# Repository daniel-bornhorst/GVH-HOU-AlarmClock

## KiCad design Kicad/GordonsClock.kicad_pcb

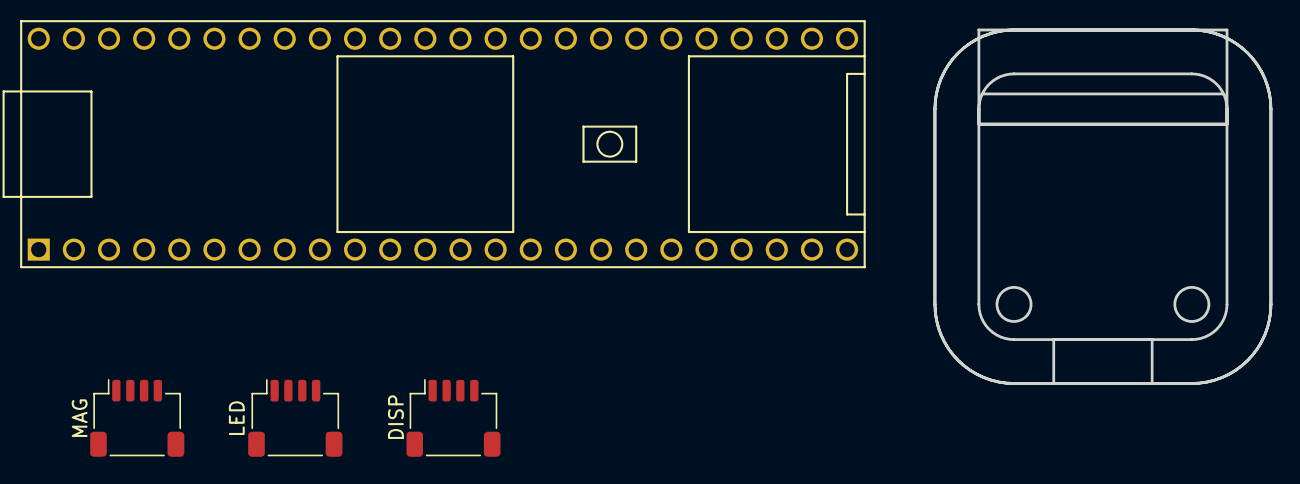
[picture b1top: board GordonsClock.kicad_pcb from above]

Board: 2 copper layers, 24.3 x 25.6 mm, 4 parts (0 on the bottom side), 8 nets, no tracks yet.

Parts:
DISP: JST_SH_SM04B-SRSS-TB_1x04-1MP_P1.00mm_Horizontal
LED: JST_SH_SM04B-SRSS-TB_1x04-1MP_P1.00mm_Horizontal
MAG: JST_SH_SM04B-SRSS-TB_1x04-1MP_P1.00mm_Horizontal
U1: Teensy4.1; Teensy41_minimal

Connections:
+3V3: DISP.2 (3.3VDC), MAG.2 (3.3VDC), U1.46 (3V3)
+5V: LED.2 (5VDC), U1.48 (VIN)
DISP_SCL: DISP.4 (SCL), U1.16 (24_A10_TX6_SCL2)
DISP_SDA: DISP.3 (SDA), U1.17 (25_A11_RX6_SDA2)
GND: DISP.1 (GND), LED.1 (GND), MAG.1 (GND), U1.1 (GND), U1.34 (GND), U1.47 (GND)
MAG_SCL: MAG.4 (SCL), U1.41 (19_A5_SCL)
MAG_SDA: MAG.3 (SDA), U1.40 (18_A4_SDA)
PIXEL_DATA: LED.3 (DATA), U1.8 (6_OUT1D)

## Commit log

2023-10-09 Added return to idle mode timeout
    After a certain amount of time the clock returns to its "Idle" state.
2023-10-09 Start in IDLE mode
2023-10-09 Refactored to use custom HT16k33 and i2c diver
    Using a non blocking i2c driver to hopefully prevent audio playback glitches.
2023-10-09 Added randomization mask and elapsedMillis timer
2023-10-09 Added character lookup and string scrolling
    Still very buggy
2023-10-09 Fixed scrolling txt rest bug
2023-10-10 Disabled Scrolling mode
2023-10-10 Using new i2c driver directy, added audio
    Using i2c driver for teensy directly vs use the Wire library wrapper.
2023-10-11 More file refactoring and organizing. Implemented display class state.
2023-10-14 Added VU meter mode, Updated animation engine, added animation
    Updated animation engine to instantly switch animations and load first frame data properly
2023-10-19 Added proper glitch animation
2023-10-19 VU Meter adjustments
2023-10-21 Added tuning pot routine, display setters
2023-10-25 Changer tuner from pot to quad encoder
2023-10-25 added auto glitch ie attract mode
2023-10-25 Completed text scrolling
2023-10-26 Changed names ie atm->sleep etc..
2023-10-26 Added a bunch of animations and one shot mode
2023-10-27 animation cleanup
2023-10-29 QTPY Branch - experimental
2023-10-29 Got it working on the py and added some animations
2023-10-30 Button and switch integration
2023-11-04 Got network working and added watchdog routine
2023-11-04 Added OSC message receive
2023-11-09 Added simple clock mode
2023-11-11 updated power couple IP
2023-11-22 code tidying
2023-11-25 Manually Merged QTPY & main branches
    NOTE: Modified teensy NativeEthernet library to keep it from hanging when no cable is plugged in.
    At line 293 Replaced:
    while(!link_status){ // original loop
    }
    With:
    uint16_t escape_counter = 0;
2023-11-30 Minute animation changes
2023-11-30 Updated minutes animation...again
2023-12-06 Added USE_NETWORK directive, cleaned up min animation
2023-12-06 Made wake animation more intricate
2023-12-08 clean up and sleep animation tweaks
2023-12-09 Added radio playback. Next need to simulate tuning.
2023-12-14 Have radio station ETNL playing back on loop
2023-12-14 Removed all network related code
2023-12-15 Added Radio tuning between three stations!!!
2023-12-16 Further Animation progress on Hour and Sleep
2023-12-16 Pretty close to done on the Hour animation
2023-12-16 Improvement on minute animation
2023-12-19 Further tweaking of minute animation
2023-12-24 radio on/off state in demo state
2024-02-23 Added Pixel Sequencer, cleaned up code
    Added state history buffer with pattern matching. This allows for secret codes to be punched in.
2024-02-24 Tightened up sleep animation, played with syncing display and pixels
2024-02-25 Refactoring some state machine logic, tightening up animations
2024-02-25 More logic tightening
2024-02-27 Secret audio mode adjustments
2024-03-02 Tightened up Sleep, Wake, and Hour per Dale's suggestions
2024-03-02 Added some more to the pixel glitch animation
2024-03-02 Added blink mode to the display class
2024-03-02 Cleaning up the clock state machine logic
    Also did some refactoring
    Removed unused code
2024-03-09 Added new secret clock modes
2024-03-09 Added the PCB design files BIG UPDATE
2024-03-09 Deployment build 1
    - Tightened up state transitions
    - Added ON, OFF, ALARM animations
    - Added radio timeout
    - Added Snooz animation toggle
2024-03-09 FINAL FINAL Deployment- Glitch was out of sync
2024-03-13 Added reboot code, changed 911 to Alert, debug print macros
2024-04-17 Fixed magnetometer speed bug. Updated Minute animation.
2024-06-15 Cleanup, probably final commit for now
